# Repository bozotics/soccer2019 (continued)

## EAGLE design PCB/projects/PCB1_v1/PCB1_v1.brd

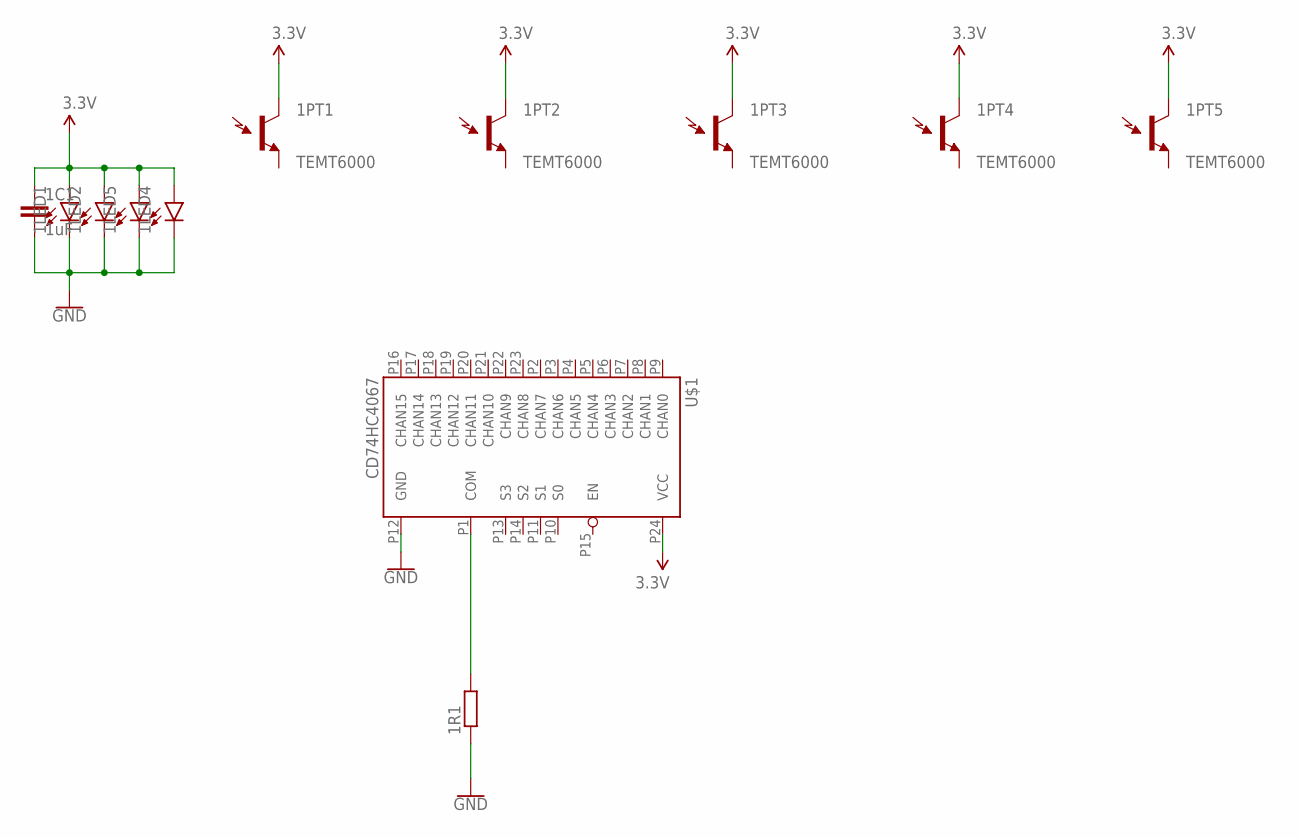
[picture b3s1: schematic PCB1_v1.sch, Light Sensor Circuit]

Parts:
1C1: 1uF; C0603
1LED1, 1LED2, 1LED4, 1LED5: 3528LED; 3528
1PT1, 1PT2, 1PT3, 1PT4, 1PT5: TEMT6000
1R1: 2k; R0603
U$1: CD74HC4067; SOIC-24

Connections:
3.3V: 1C1.1, 1LED1.A, 1LED2.A, 1LED4.A, 1LED5.A, 1PT1.COLLECTOR (C1), 1PT2.COLLECTOR (C1), 1PT3.COLLECTOR (C1), 1PT4.COLLECTOR (C1), 1PT5.COLLECTOR (C1), U$1.P24 (VCC)
GND: 1C1.2, 1LED1.C, 1LED2.C, 1LED4.C, 1LED5.C, 1R1.1, U$1.P12 (GND)
unnamed: 1R1.2, U$1.P1 (COM)

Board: 2 copper layers, 12 parts (0 on the bottom side), 3 nets, no tracks yet.

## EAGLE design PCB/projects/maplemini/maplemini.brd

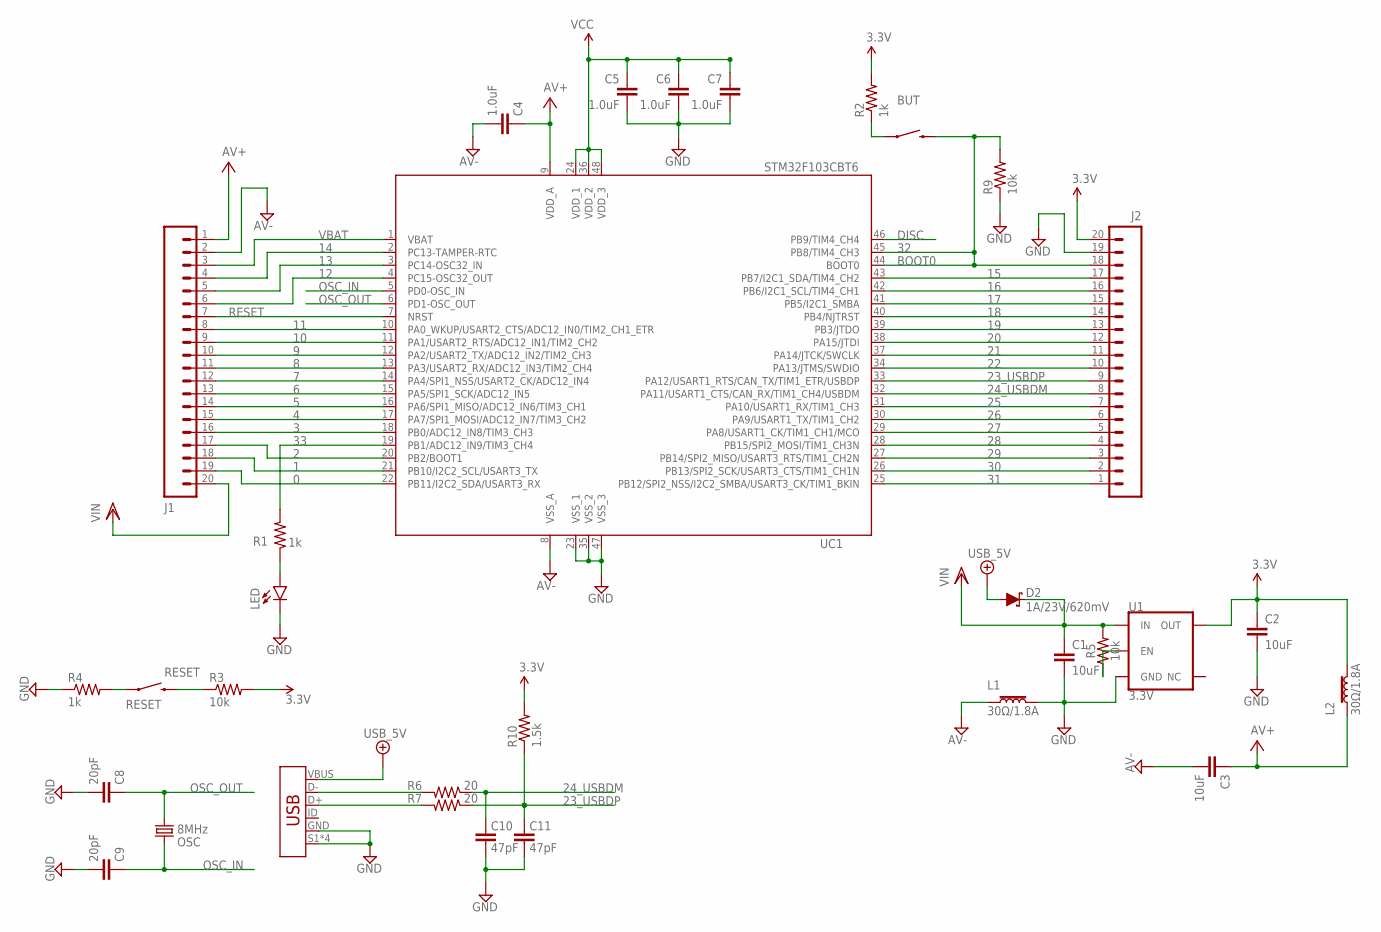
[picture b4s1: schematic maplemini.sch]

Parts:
BUT: KMR211GLFS; 3*4-MOMENTARY-SWITCH
C1, C2, C3: 10uF; 0603
C4, C5, C6, C7: 1.0uF; 0603
C8, C9: 20pF; 0603
C10, C11: 47pF; 0603
D2: 1A/23V/620mV; SOD-323
J1, J2: CONN_20LOCK; 1X20_LOCK
L1, L2: 30Ω/1.8A; 0603
LED: RED; LED-1206
OSC: 8MHz; CRYSTAL-SMD-5X3.2-2PAD
R1, R2, R4: 1k; 0603
R3, R5, R9: 10k; 0603
R6, R7: 20; 0603
R10: 1.5k; 0603
RESET: KMR211GLFS; 3*4-MOMENTARY-SWITCH
U1: 3.3V; SOT23-5
UC1: STM32F103CBT6; LQFP48
X1: USB-MINIB

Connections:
0: J1.19, UC1.22 (PB11/I2C2_SDA/USART3_RX)
1: J1.18, UC1.21 (PB10/I2C2_SCL/USART3_TX)
2: J1.17, UC1.20 (PB2/BOOT1)
3: J1.16, UC1.18 (PB0/ADC12_IN8/TIM3_CH3)
4: J1.15, UC1.17 (PA7/SPI1_MOSI/ADC12_IN7/TIM3_CH2)
5: J1.14, UC1.16 (PA6/SPI1_MISO/ADC12_IN6/TIM3_CH1)
6: J1.13, UC1.15 (PA5/SPI1_SCK/ADC12_IN5)
7: J1.12, UC1.14 (PA4/SPI1_NSS/USART2_CK/ADC12_IN4)
8: J1.11, UC1.13 (PA3/USART2_RX/ADC12_IN3/TIM2_CH4)
9: J1.10, UC1.12 (PA2/USART2_TX/ADC12_IN2/TIM2_CH3)
10: J1.9, UC1.11 (PA1/USART2_RTS/ADC12_IN1/TIM2_CH2)
11: J1.8, UC1.10 (PA0_WKUP/USART2_CTS/ADC12_IN0/TIM2_CH1_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)
12: J1.6, UC1.4 (PC15-OSC32_OUT)
13: J1.5, UC1.3 (PC14-OSC32_IN)
14: J1.4, UC1.2 (PC13-TAMPER-RTC)
15: J2.17, UC1.43 (PB7/I2C1_SDA/TIM4_CH2)
16: J2.16, UC1.42 (PB6/I2C1_SCL/TIM4_CH1)
17: J2.15, UC1.41 (PB5/I2C1_SMBA)
18: J2.14, UC1.40 (PB4/NJTRST)
19: J2.13, UC1.39 (PB3/JTDO)
20: J2.12, UC1.38 (PA15/JTDI)
21: J2.11, UC1.37 (PA14/JTCK/SWCLK)
22: J2.10, UC1.34 (PA13/JTMS/SWDIO)
23_USBDP: C11.2, J2.9, R7.1, R10.1, UC1.33 (PA12/USART1_RTS/CAN_TX/TIM1_ETR/USBDP)
24_USBDM: C10.2, J2.8, R6.1, UC1.32 (PA11/USART1_CTS/CAN_RX/TIM1_CH4/USBDM)
25: J2.7, UC1.31 (PA10/USART1_RX/TIM1_CH3)
26: J2.6, UC1.30 (PA9/USART1_TX/TIM1_CH2)
27: J2.5, UC1.29 (PA8/USART1_CK/TIM1_CH1/MCO)
28: J2.4, UC1.28 (PB15/SPI2_MOSI/TIM1_CH3N)
29: J2.3, UC1.27 (PB14/SPI2_MISO/USART3_RTS/TIM1_CH2N)
30: J2.2, UC1.26 (PB13/SPI2_SCK/USART3_CTS/TIM1_CH1N)
31: J2.1, UC1.25 (PB12/SPI2_NSS/I2C2_SMBA/USART3_CK/TIM1_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)
32: BUT.P2 (2), J2.18, R9.2, UC1.44 (BOOT0), UC1.45 (PB8/TIM4_CH3)
33: R1.2, UC1.19 (PB1/ADC12_IN9/TIM3_CH4)
+5V/2: D2.A, X1.VBUS
AV+: C3.1, C4.1, J1.1, L2.1, UC1.9 (VDD_A)
AV-: C3.2, C4.2, J1.2, L1.1, UC1.8 (VSS_A)
DGND: C1.2, C2.2, C5.2, C6.2, C7.2, C8.2, C9.2, C10.1, C11.1, J2.19, L1.2, LED.C, R4.1, R9.1, U1.2 (GND), UC1.23 (VSS_1), UC1.35 (VSS_2), UC1.47 (VSS_3), X1.GND, X1.S1 (SHIELD), X1.S2 (SHIELD), X1.S3 (SHIELD), X1.S4 (SHIELD)
DISC: UC1.46 (PB9/TIM4_CH4)
unnamed: BUT.P1 (1), R2.1
unnamed: LED.A, R1.1
unnamed: R5.1, U1.3 (EN)
unnamed: R4.2, RESET.P1 (1)
unnamed: R6.2, X1.D-
unnamed: R7.2, X1.D+
OSC_IN: C9.1, OSC.P$2 (2), UC1.5 (PD0-OSC_IN)
OSC_OUT: C8.1, OSC.P$1 (1), UC1.6 (PD1-OSC_OUT)
RESET: J1.7, R3.1, RESET.P2 (2), UC1.7 (NRST)
VBAT: J1.3, UC1.1 (VBAT)
VCC: C2.1, C5.1, C6.1, C7.1, J2.20, L2.2, R2.2, R3.2, R10.2, U1.5 (OUT), UC1.24 (VDD_1), UC1.36 (VDD_2), UC1.48 (VDD_3)
VIN: C1.1, D2.C, J1.20, R5.2, U1.1 (IN)

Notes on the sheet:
BOOT0

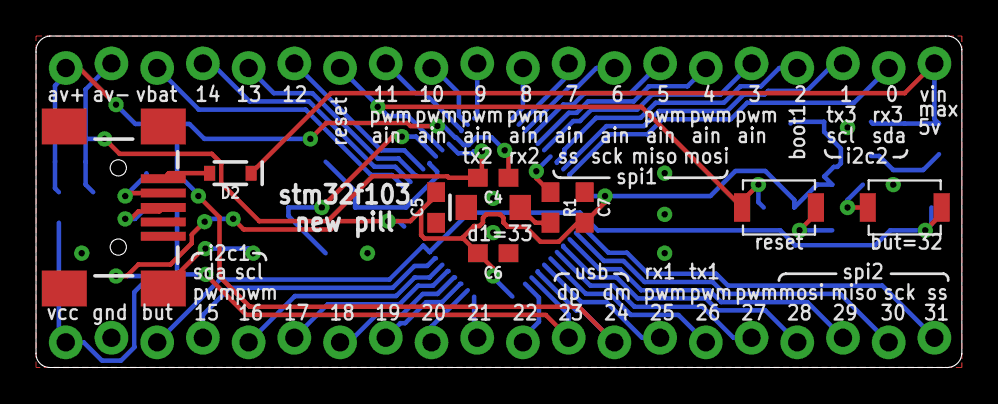
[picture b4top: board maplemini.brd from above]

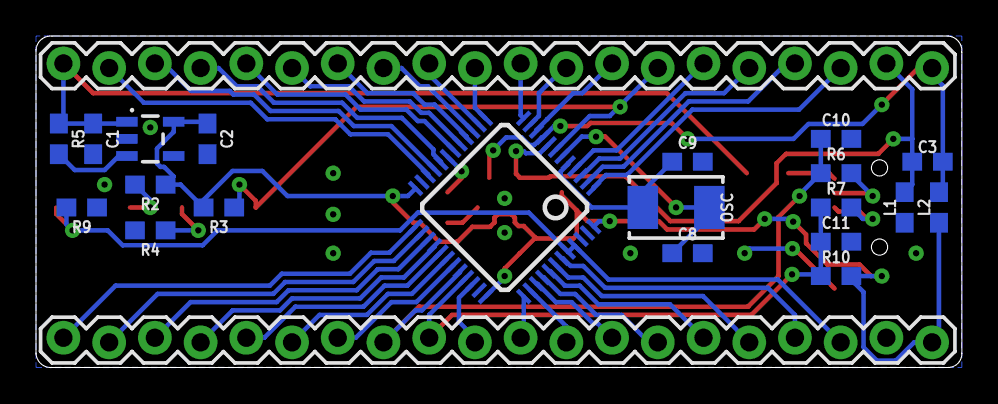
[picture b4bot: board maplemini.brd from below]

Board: 2 copper layers, 51.4 x 18.4 mm, 32 parts (22 on the bottom side), 50 nets.

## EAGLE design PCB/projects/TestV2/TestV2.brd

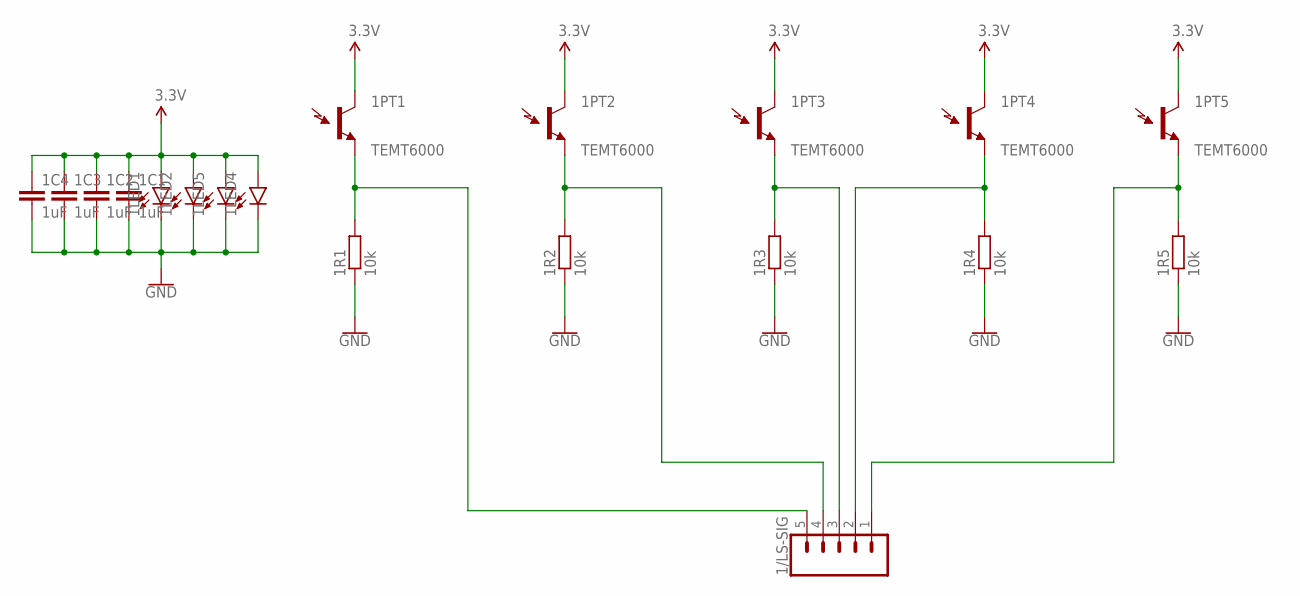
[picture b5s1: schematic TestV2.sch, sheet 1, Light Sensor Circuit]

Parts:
1/LS-SIG: CONN_05LOCK; 1X05_LOCK
1C1, 1C2, 1C3, 1C4: 1uF; C0603
1LED1, 1LED2, 1LED4, 1LED5: 3528LED; 3528
1PT1, 1PT2, 1PT3, 1PT4, 1PT5: TEMT6000
1R1, 1R2, 1R3, 1R4, 1R5: 10k; R0603

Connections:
3.3V: 1C1.1, 1C2.1, 1C3.1, 1C4.1, 1LED1.A, 1LED2.A, 1LED4.A, 1LED5.A, 1PT1.COLLECTOR (C1), 1PT2.COLLECTOR (C1), 1PT3.COLLECTOR (C1), 1PT4.COLLECTOR (C1), 1PT5.COLLECTOR (C1); also elsewhere on the board
GND: 1C1.2, 1C2.2, 1C3.2, 1C4.2, 1LED1.C, 1LED2.C, 1LED4.C, 1LED5.C, 1R1.1, 1R2.1, 1R3.1, 1R4.1, 1R5.1; also elsewhere on the board
unnamed: 1/LS-SIG.4, 1PT2.EMITTER (E1), 1R2.2
unnamed: 1/LS-SIG.3, 1PT3.EMITTER (E1), 1R3.2
unnamed: 1/LS-SIG.2, 1PT4.EMITTER (E1), 1R4.2
unnamed: 1/LS-SIG.1, 1PT5.EMITTER (E1), 1R5.2
unnamed: 1/LS-SIG.5, 1PT1.EMITTER (E1), 1R1.2

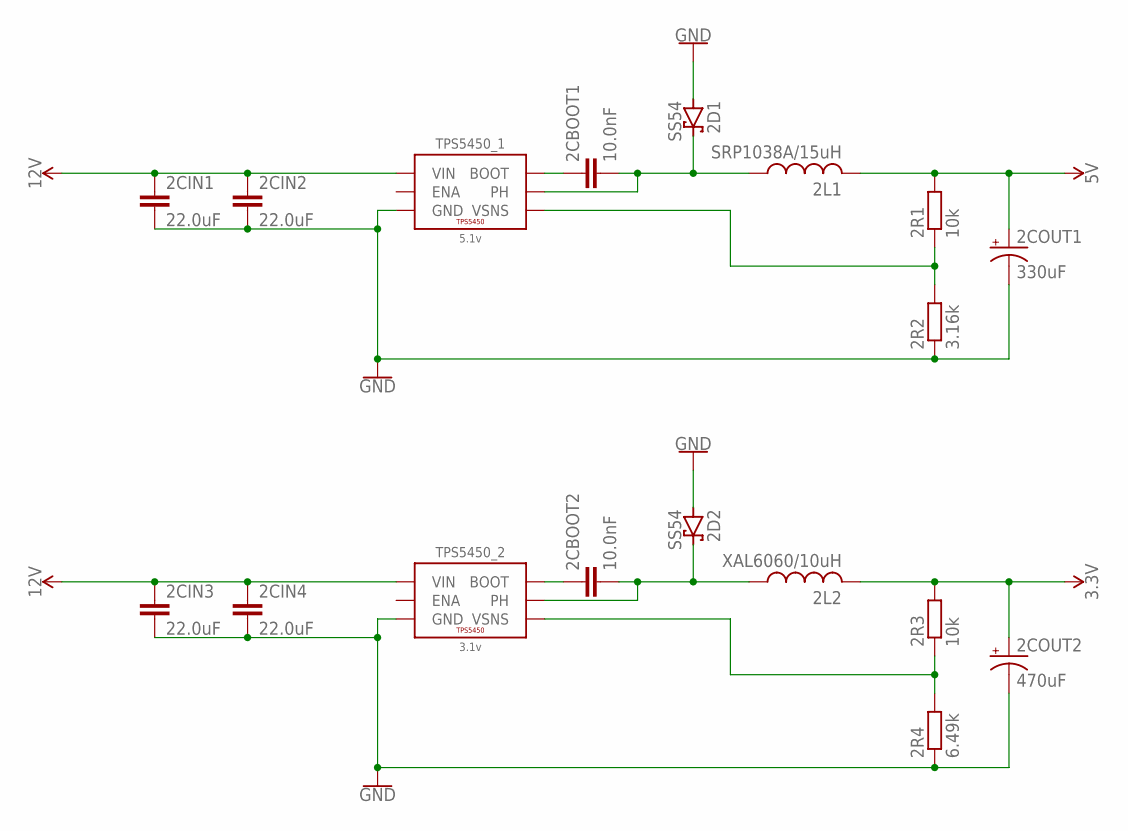
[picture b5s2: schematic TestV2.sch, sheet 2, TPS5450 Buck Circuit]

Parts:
2CBOOT1, 2CBOOT2: 10.0nF; C0603
2CIN1, 2CIN2, 2CIN3, 2CIN4: 22.0uF; C1210
2COUT1: 330uF; D/7343-31R
2COUT2: 470uF; D/7343-31R
2D1, 2D2: SS54; SMB
2L1: SRP1038A/15uH; SRP1038A
2L2: XAL6060/10uH; XAL6060
2R1, 2R3: 10k; R0603
2R2: 3.16k; R0603
2R4: 6.49k; R0603
TPS5450_1: 5.1v; POWERPAD-SOIC-8
TPS5450_2: 3.1v; POWERPAD-SOIC-8

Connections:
3.3V: 2COUT2.+, 2L2.2, 2R3.2; also elsewhere on the board
5V: 2COUT1.+, 2L1.2, 2R1.2; also elsewhere on the board
12V: 2CIN1.1, 2CIN2.1, 2CIN3.1, 2CIN4.1, TPS5450_1.7 (VIN), TPS5450_2.7 (VIN); also elsewhere on the board
GND: 2CIN1.2, 2CIN2.2, 2CIN3.2, 2CIN4.2, 2COUT1.-, 2COUT2.-, 2D1.A, 2D2.A, 2R2.1, 2R4.1, TPS5450_1.6 (GND), TPS5450_1.9 (GND), TPS5450_1.P$1 (GND), TPS5450_1.P$2 (GND), TPS5450_1.P$3 (GND), TPS5450_1.P$4 (GND), TPS5450_1.P$5 (GND), TPS5450_1.P$6 (GND), TPS5450_2.6 (GND), TPS5450_2.9 (GND), TPS5450_2.P$1 (GND), TPS5450_2.P$2 (GND), TPS5450_2.P$3 (GND), TPS5450_2.P$4 (GND), TPS5450_2.P$5 (GND), TPS5450_2.P$6 (GND); also elsewhere on the board
unnamed: 2CBOOT1.2, 2D1.C, 2L1.1, TPS5450_1.8 (PH)
unnamed: 2CBOOT2.1, TPS5450_2.1 (BOOT)
unnamed: 2CBOOT1.1, TPS5450_1.1 (BOOT)
unnamed: 2R1.1, 2R2.2, TPS5450_1.4 (VSNS)
unnamed: 2CBOOT2.2, 2D2.C, 2L2.1, TPS5450_2.8 (PH)
unnamed: 2R3.1, 2R4.2, TPS5450_2.4 (VSNS)

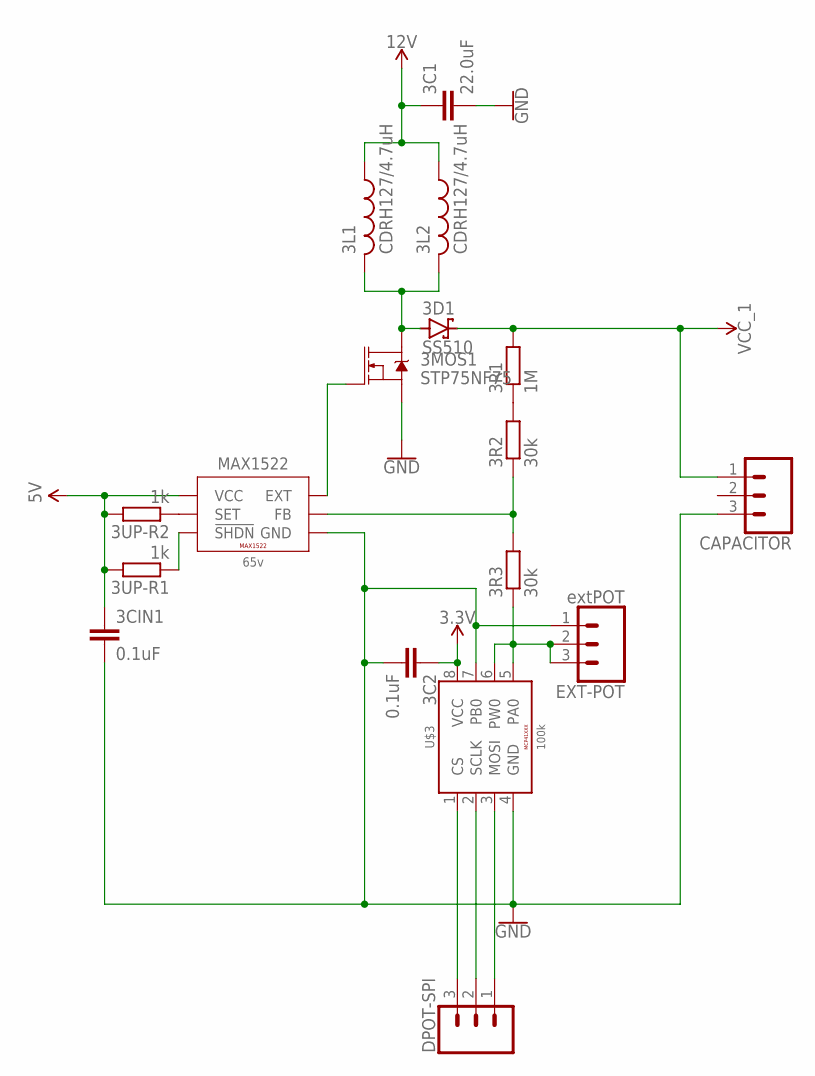
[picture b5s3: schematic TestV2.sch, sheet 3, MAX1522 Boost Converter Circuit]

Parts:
3C1: 22.0uF; C1210
3C2, 3CIN1: 0.1uF; C0603
3D1: SS510; SMB
3L1, 3L2: CDRH127/4.7uH; 127
3MOS1: STP75NF75; TO220V
3R1: 1M; R0603
3R2, 3R3: 30k; R0603
3UP-R1, 3UP-R2: 1k; R0603
CAPACITOR: CONN_03-SCREW-5MM; SCREWTERMINAL-5MM-3
DPOT-SPI: CONN_03LOCK; 1X03_LOCK
EXT-POT: extPOT; 1X03
MAX1522: 65v; SOT23-6
U$3: 100k; SOIC-8

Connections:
3.3V: 3C2.1, U$3.8 (VCC); also elsewhere on the board
5V: 3CIN1.1, 3UP-R1.2, 3UP-R2.2, MAX1522.6 (VCC); also elsewhere on the board
12V: 3C1.1, 3L1.1, 3L2.1; also elsewhere on the board
GND: 3C1.2, 3C2.2, 3CIN1.2, 3MOS1.3 (S), CAPACITOR.3, EXT-POT.1, MAX1522.1 (GND), U$3.4 (GND), U$3.7 (PB0); also elsewhere on the board
unnamed: 3R1.1, 3R2.2
unnamed: 3R2.1, 3R3.2, MAX1522.2 (FB)
unnamed: 3MOS1.1 (G), MAX1522.5 (EXT)
unnamed: 3R3.1, EXT-POT.2, EXT-POT.3, U$3.5 (PA0), U$3.6 (PW0)
unnamed: 3D1.A, 3L1.2, 3L2.2, 3MOS1.2 (D)
unnamed: 3UP-R1.1, MAX1522.4 (!SHDN)
unnamed: 3UP-R2.1, MAX1522.3 (SET)
unnamed: DPOT-SPI.3, U$3.1 (CS)
unnamed: DPOT-SPI.2, U$3.2 (SCLK)
unnamed: DPOT-SPI.1, U$3.3 (MOSI)
VCC_1: 3D1.C, 3R1.2, CAPACITOR.1; also elsewhere on the board

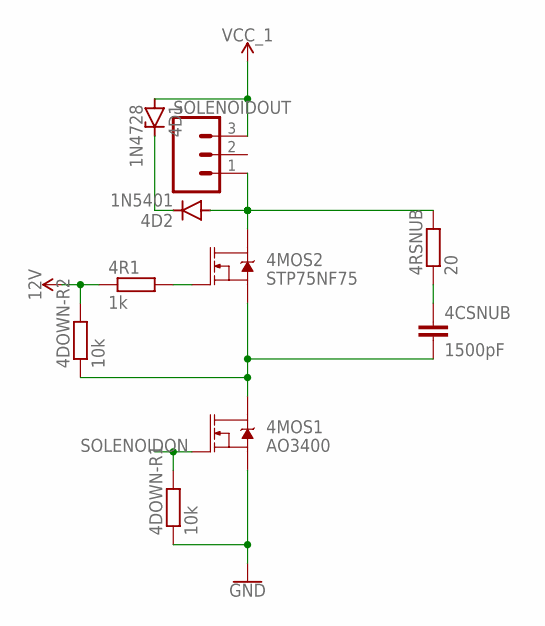
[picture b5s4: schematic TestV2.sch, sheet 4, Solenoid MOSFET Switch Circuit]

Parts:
4CSNUB: 1500pF; C0603
4D1: 1N4728; DO41Z10
4D2: 1N5401; DO201-15
4DOWN-R1, 4DOWN-R2: 10k; R0603
4MOS1: AO3400; SOT23-3
4MOS2: STP75NF75; TO220V
4R1: 1k; R0603
4RSNUB: 20; R0603
SOLENOIDOUT: CONN_03-SCREW-5MM; SCREWTERMINAL-5MM-3

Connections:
12V: 4DOWN-R2.2, 4R1.1; also elsewhere on the board
GND: 4DOWN-R1.1, 4MOS1.2 (S); also elsewhere on the board
unnamed: 4CSNUB.2, 4DOWN-R2.1, 4MOS1.3 (D), 4MOS2.3 (S)
unnamed: 4MOS2.1 (G), 4R1.2
unnamed: 4D1.C, 4D2.C
unnamed: 4CSNUB.1, 4RSNUB.1
SOLENOID-: 4D2.A, 4MOS2.2 (D), 4RSNUB.2, SOLENOIDOUT.1
SOLENOIDON: 4DOWN-R1.2, 4MOS1.1 (G); also elsewhere on the board
VCC_1: 4D1.A, SOLENOIDOUT.3; also elsewhere on the board

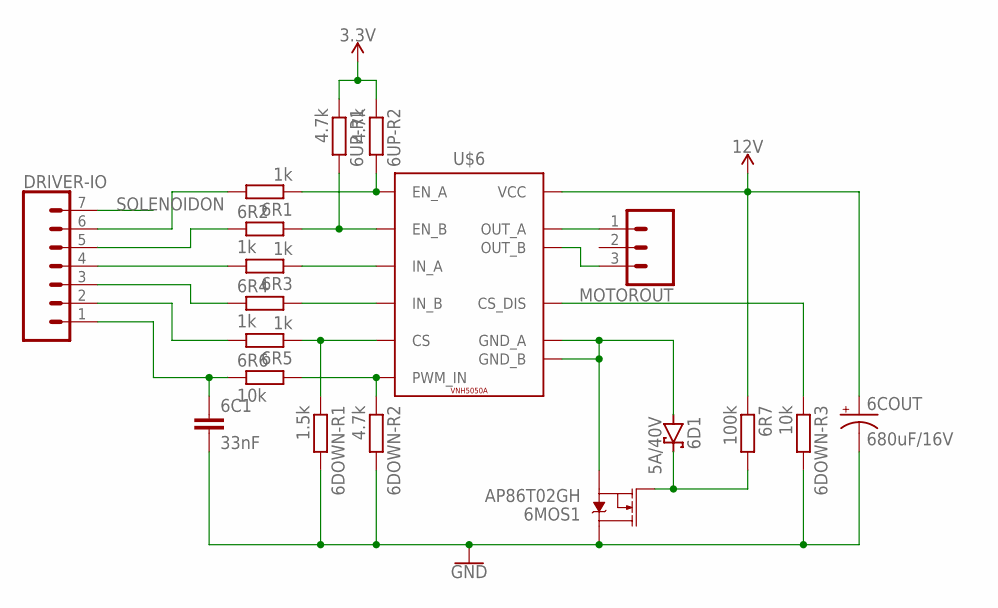
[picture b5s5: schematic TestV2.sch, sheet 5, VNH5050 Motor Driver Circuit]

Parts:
6C1: 33nF; C0603
6COUT: 680uF/16V; E3,5-8
6D1: 5A/40V; SMB
6DOWN-R1: 1.5k; R0603
6DOWN-R2, 6UP-R1, 6UP-R2: 4.7k; R0603
6DOWN-R3, 6R6: 10k; R0603
6MOS1: AP86T02GH; DPAK
6R1, 6R2, 6R3, 6R4, 6R5: 1k; R0603
6R7: 100k; R0603
DRIVER-IO: CONN_07LOCK; 1X07_LOCK
MOTOROUT: CONN_03-SCREW-5MM; SCREWTERMINAL-5MM-3
U$6: VNH5050A; POWERSSO-36

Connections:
3.3V: 6UP-R1.1, 6UP-R2.1; also elsewhere on the board
12V: 6COUT.+, 6R7.1, U$6.1 (VCC), U$6.P13 (VCC), U$6.P24 (VCC), U$6.P$13 (VCC), U$6.P$14 (VCC), U$6.P$15 (VCC), U$6.P$16 (VCC), U$6.P$17 (VCC), U$6.P$18 (VCC), U$6.P$19 (VCC), U$6.P$20 (VCC), U$6.P$21 (VCC), U$6.P$22 (VCC), U$6.P$23 (VCC), U$6.P$24 (VCC); also elsewhere on the board
CS: 6R5.2, DRIVER-IO.2
EN_A: 6R1.2, DRIVER-IO.6
EN_B: 6R2.1, DRIVER-IO.5
GND: 6C1.2, 6COUT.-, 6DOWN-R1.2, 6DOWN-R2.2, 6DOWN-R3.2, 6MOS1.4 (D); also elsewhere on the board
IN_A: 6R3.2, DRIVER-IO.4
IN_B: 6R4.1, DRIVER-IO.3
unnamed: 6R1.1, 6UP-R2.2, U$6.P16 (EN_A)
unnamed: 6R3.1, U$6.P15 (IN_A)
unnamed: 6R2.2, 6UP-R1.2, U$6.P21 (EN_B)
unnamed: 6R4.2, U$6.P22 (IN_B)
unnamed: 6DOWN-R2.1, 6R6.2, U$6.P17 (PWM_IN)
unnamed: 6DOWN-R1.1, 6R5.1, U$6.P19 (CS)
unnamed: 6D1.A, 6MOS1.3 (S), U$6.P1 (GND_A), U$6.P3 (GND_A), U$6.P4 (GND_A), U$6.P5 (GND_A), U$6.P6 (GND_A), U$6.P7 (GND_A), U$6.P30 (GND_B), U$6.P31 (GND_B), U$6.P32 (GND_B), U$6.P33 (GND_B), U$6.P34 (GND_B), U$6.P36 (GND_B)
unnamed: 6D1.C, 6MOS1.1 (G), 6R7.2
unnamed: 6DOWN-R3.1, U$6.P20 (CS_DIS)
unnamed: MOTOROUT.1, U$6.2 (OUT_A), U$6.P2 (OUT_A), U$6.P8 (OUT_A), U$6.P9 (OUT_A), U$6.P10 (OUT_A), U$6.P11 (OUT_A), U$6.P12 (OUT_A), U$6.P14 (OUT_A), U$6.P$7 (OUT_A), U$6.P$8 (OUT_A), U$6.P$9 (OUT_A), U$6.P$10 (OUT_A), U$6.P$11 (OUT_A), U$6.P$12 (OUT_A)
unnamed: MOTOROUT.3, U$6.3 (OUT_B), U$6.P23 (OUT_B), U$6.P25 (OUT_B), U$6.P26 (OUT_B), U$6.P27 (OUT_B), U$6.P28 (OUT_B), U$6.P29 (OUT_B), U$6.P35 (OUT_B), U$6.P$1 (OUT_B), U$6.P$2 (OUT_B), U$6.P$3 (OUT_B), U$6.P$4 (OUT_B), U$6.P$5 (OUT_B), U$6.P$6 (OUT_B)
PWM: 6C1.1, 6R6.1, DRIVER-IO.1
SOLENOIDON: DRIVER-IO.7; also elsewhere on the board

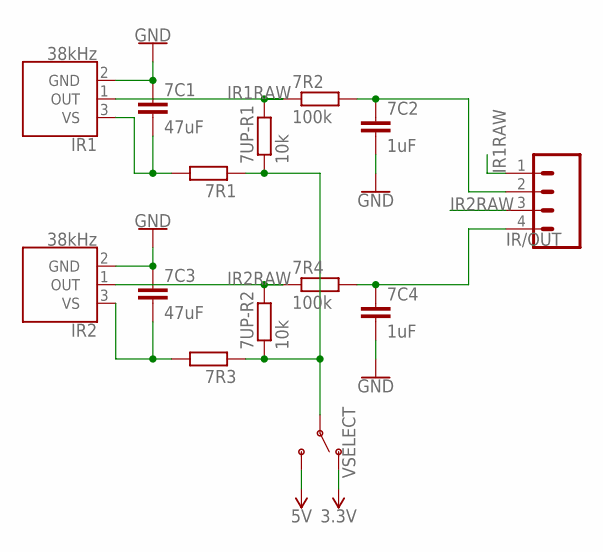
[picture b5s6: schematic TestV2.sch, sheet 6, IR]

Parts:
7C1, 7C3: 47uF; C0603
7C2, 7C4: 1uF; C0603
7R1, 7R3: R-EU_R0603; R0603
7R2, 7R4: 100k; R0603
7UP-R1, 7UP-R2: 10k; R0603
IR1, IR2: 38kHz; TSOP382
IR/OUT: CONN_04LOCK; 1X04_LOCK
VSELECT: SWITCH-SPDT-PTH-11.6X4.0MM-LOCK; SWITCH_SPDT_PTH_11.6X4.0MM_LOCK

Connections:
3.3V: VSELECT.1 (O); also elsewhere on the board
5V: VSELECT.3 (S); also elsewhere on the board
GND: 7C1.1, 7C2.2, 7C3.1, 7C4.2, IR1.2 (GND), IR2.2 (GND); also elsewhere on the board
IR1RAW: 7R2.1, 7UP-R1.2, IR1.1 (OUT), IR/OUT.1
IR2RAW: 7R4.1, 7UP-R2.2, IR2.1 (OUT), IR/OUT.3
unnamed: 7C1.2, 7R1.2, IR1.3 (VS)
unnamed: 7R1.1, 7R3.1, 7UP-R1.1, 7UP-R2.1, VSELECT.2
unnamed: 7C2.1, 7R2.2, IR/OUT.2
unnamed: 7C3.2, 7R3.2, IR2.3 (VS)
unnamed: 7C4.1, 7R4.2, IR/OUT.4

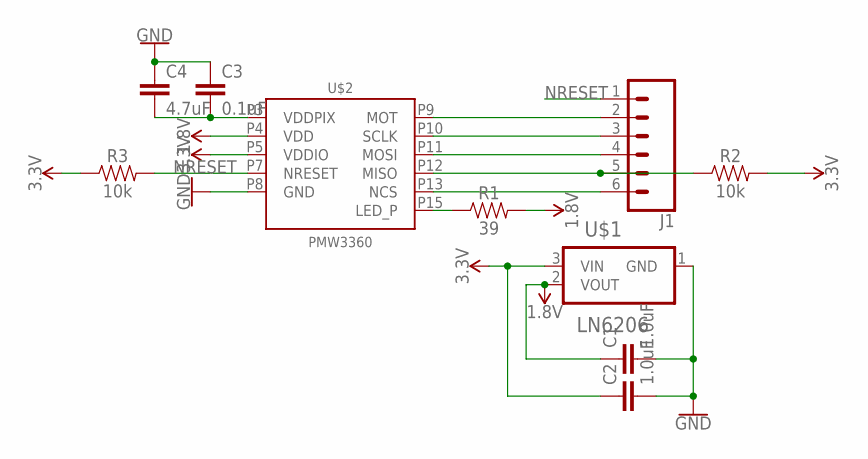
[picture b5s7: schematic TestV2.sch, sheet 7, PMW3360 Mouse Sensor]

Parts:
C1, C2: 1.0uF; 0603
C3: 0.1uF; 0603
C4: 4.7uF; 0603
J1: CONN_06LOCK; 1X06_LOCK
R1: 39; 0603
R2, R3: 10k; 0603
U$1: LN6206; SOT95P237X112-3N
U$2: PMW3360

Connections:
1.8V: C1.1, R1.2, U$1.2 (VOUT), U$2.P4 (VDD)
3.3V: C2.1, R2.2, R3.1, U$1.3 (VIN), U$2.P5 (VDDIO); also elsewhere on the board
GND: C1.2, C2.2, C3.1, C4.1, U$1.1 (GND), U$2.P8 (GND); also elsewhere on the board
unnamed: R1.1, U$2.P15 (LED_P)
unnamed: J1.6, U$2.P13 (NCS)
unnamed: J1.5, R2.1, U$2.P12 (MISO)
unnamed: J1.4, U$2.P11 (MOSI)
unnamed: J1.3, U$2.P10 (SCLK)
unnamed: J1.2, U$2.P9 (MOT)
unnamed: C3.2, C4.2, U$2.P3 (VDDPIX)
NRESET: J1.1, R3.2, U$2.P7 (NRESET)

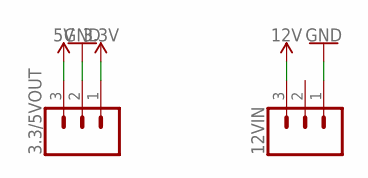
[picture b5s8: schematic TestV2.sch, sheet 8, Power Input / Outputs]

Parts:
3.3/5VOUT, 12VIN: CONN_03-SCREW-5MM; SCREWTERMINAL-5MM-3

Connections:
3.3V: 3.3/5VOUT.1; also elsewhere on the board
5V: 3.3/5VOUT.3; also elsewhere on the board
12V: 12VIN.3; also elsewhere on the board
GND: 3.3/5VOUT.2, 12VIN.1; also elsewhere on the board

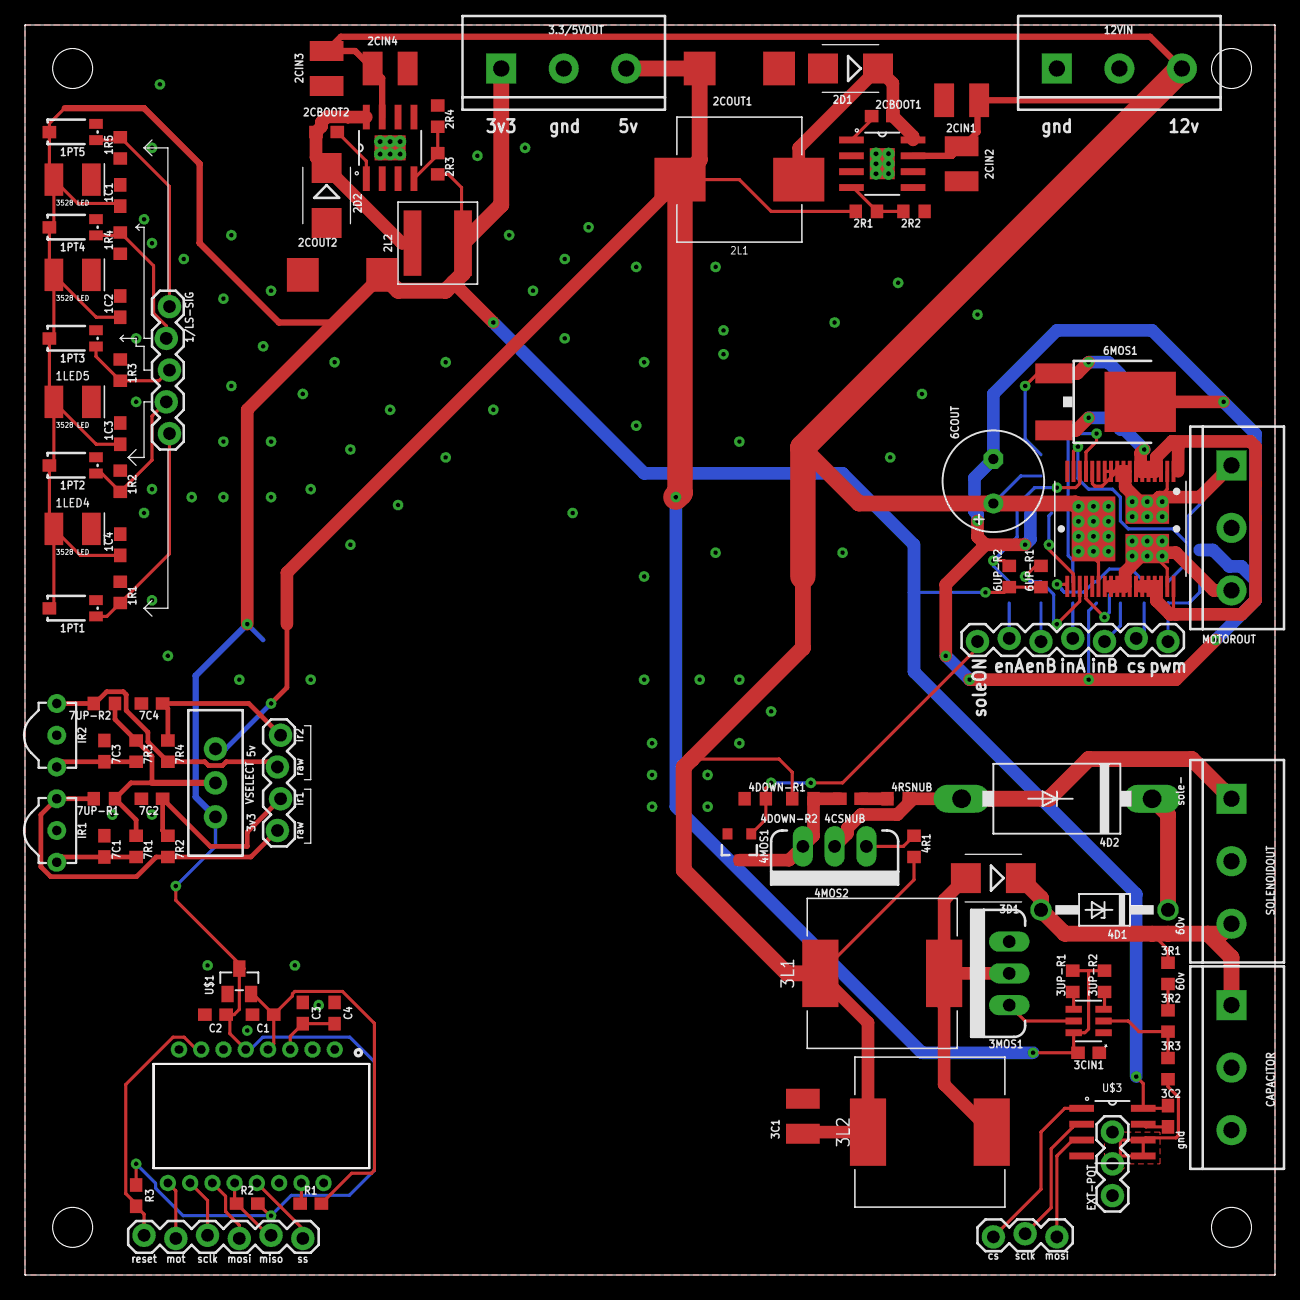
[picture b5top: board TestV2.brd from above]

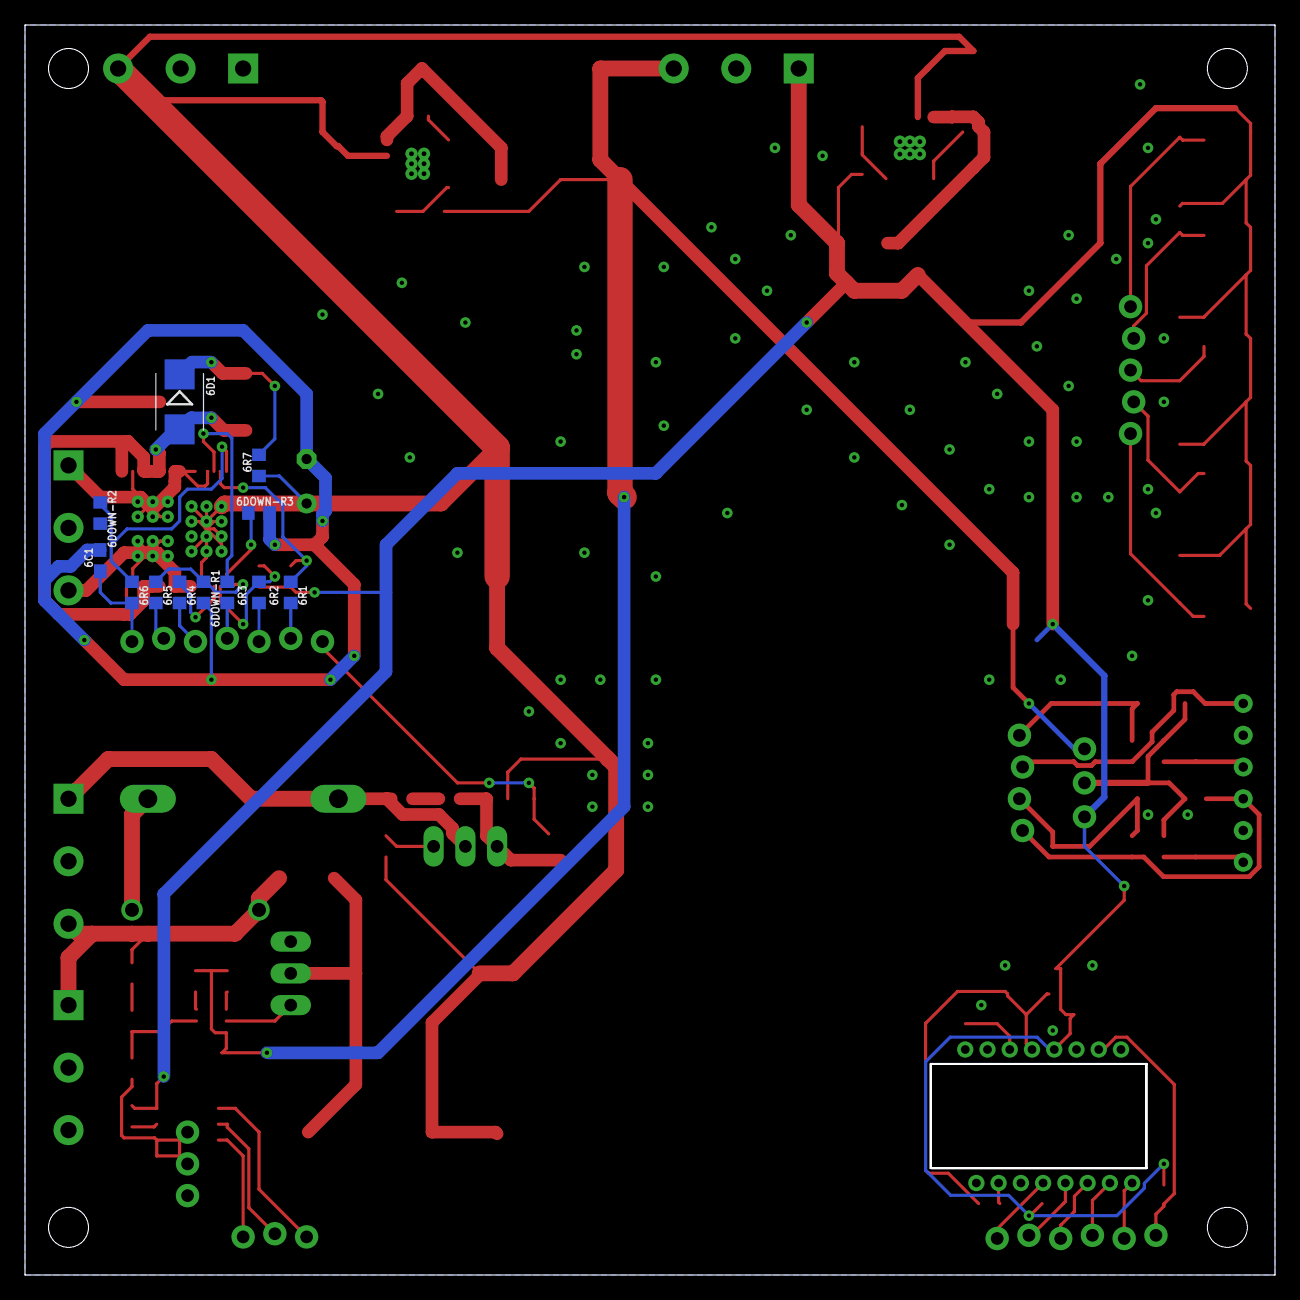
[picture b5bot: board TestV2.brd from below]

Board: 2 copper layers, 100.0 x 100.0 mm, 109 parts (12 on the bottom side), 65 nets.

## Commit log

2018-10-21 Create LICENSE
2018-10-28 Add Library Support for some components
2018-10-28 Add PCB Library for MAX1522
2018-10-28 Add Documentation for parts used
2018-11-17 TPS5450 schematic sheet done and others
2018-11-18 0.1% progress
2018-11-30 left new pill and adxl, cleaned up some symbols and wrong net names, have to make breakout pins for data pins
2018-12-03 Naming Scheme Off but 1stLayer2018v1: dead (analogMUX circuit is wrong by the way) Test V1: Schematic which will be used to implement final board Test V2: Deleted MUX and ADXL which will confirm work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
2018-12-03 update datasheets
2018-12-05 5/12 PCB Damn proper title names now Made naming a little more consistent not standard but at least I know what's happening [sch sheet number][component prefix][number] did a little board design most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
2018-12-05 cleanup and add .gitignore delete autosave files and derped pdf
2018-12-05 Cleanup even more
2018-12-08 8/12 PCB well well well so drunk the original commit name was 9/12 renamed all parts in schematic, then everything went downhill welp was in 1mm grid instead of 1.27mm forgot to check drc before rout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
2018-12-11 11/12 PCB Updated own DRU file Updated even more stuff in schematic but quite minor, mostly flipping the 5mm screw terminal connections redid the pcb kinda redid the layout and managed to frkin manua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
2018-12-16 16/12 PCB shit too much happened shld have committed more often but wtv deleted stm32 sheet added IR and mouse sensor Finally routed everything, gerber files are included hopefully done for now
2018-12-16 16/12 PCB maple mini clone Credits to maple mini for their original design, pretty much took it removed some usb circuitry to make it 2 layered and changed some components only
2018-12-16 16/12 PCB CAM file update
2018-12-16 Update PCB Library too much happened this the latest update
2019-02-04 5/2 PCB v0.0
2019-02-24 24/2 PCB v0.2 Finished new VNH5019 Motor Driver circuit, step up/down + solenoid, left with light sensors (+MUX+Comparators) and other sensors and connections. lesgo
2019-03-14 14/3 PCB v0.5 Finished all the schematics and started placing parts on PCB2.
2019-03-14 15/3 Updated the schematics, labelled of PCB2
2019-03-17 17/3 Updated derp in Boost Circuit voltage selection, updated boards even further
2019-03-17 18/3 Moved boost circuit and solenoid circuits to PCB2 else no space
2019-03-18 18/3 PCB mostly updated PCB1 layout
2019-03-18 19/3 Finally finished PCB everything gerber in here too bye maybe make a 3d model sometime when im free
2019-03-24 24/3 Added schematics PDF and addHoles ULP
2020-05-06 oopsies
    realised that the program wasn't uploaded
    no clue what's the difference between the 2 final programs tbh
